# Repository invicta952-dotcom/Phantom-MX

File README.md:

# Phantom-MX

##   what is this??
Phantom-mx is cutom made keyboard with 87 mechincal switches, roatary encoder and custom built case and qmk firmware. It has 2 layer of functions to switch between as per your need. the case type is integrated plate mount which mean you dont need to lock the plate with case with 1000's of screw

---
##   why phantom-mx??
you may find many other custom keyboard with more features and better than this, but the one thing you will never find is perfect keyboard which is in budget and also meet your needs perfectly. it was built to meet my needs and also in budget. 
<br>
**bonus point**:- it has some really cool silkscreen

---
##   how to assemble it??
### 1. Ordering the PCB
1. **Download Production Files**: Navigate to the `PCB/` directory in this repository and download the Gerber zip file (e.g., `Gerber_Phantom-MX.zip`). Do not extract it.
2. **Choose a Manufacturer**: Upload the zip file to a PCB fabrication service such as JLCPCB, PCBWay, or OSH Park.
3. **Configure Board Settings**: Use the following standard specifications:
   * **Layers**: 2 Layers
   * **Thickness**: 1.6 mm
   * **Surface Finish**: HASL (or ENIG for better pad durability)
4. **Assembly (Optional)**: If you prefer factory assembly for surface-mount components (diodes/sockets), upload the BOM (Bill of Materials) and CPL (Component Placement List / Centroid file) provided in the repository to their PCBA service.

---

### 3. Hardware Assembly
1. **Solder Diodes**: Always solder small, low-profile components first. solder the diodes before the swithces for easy soldering.
2. **Solder Sockets/Switches**: solder the switches by passing them from top plate and then top layer of pcb.
3. **Mount the Pi Pico**: Place the Pi Pico onto its designated footprint. solder it in backside of the pcb.

---
# Images

#   case

---

#   zine

---

#   pcb

<br>
<br>
<br>
onshape link <br>
https://cad.onshape.com/documents/175f6b23ffbe170e5e8f7975/w/d68c6b2354c565e22789bc76/e/012a72f814c196a96be20986?renderMode=0&uiState=6a2fc775a442fa85ac58f430

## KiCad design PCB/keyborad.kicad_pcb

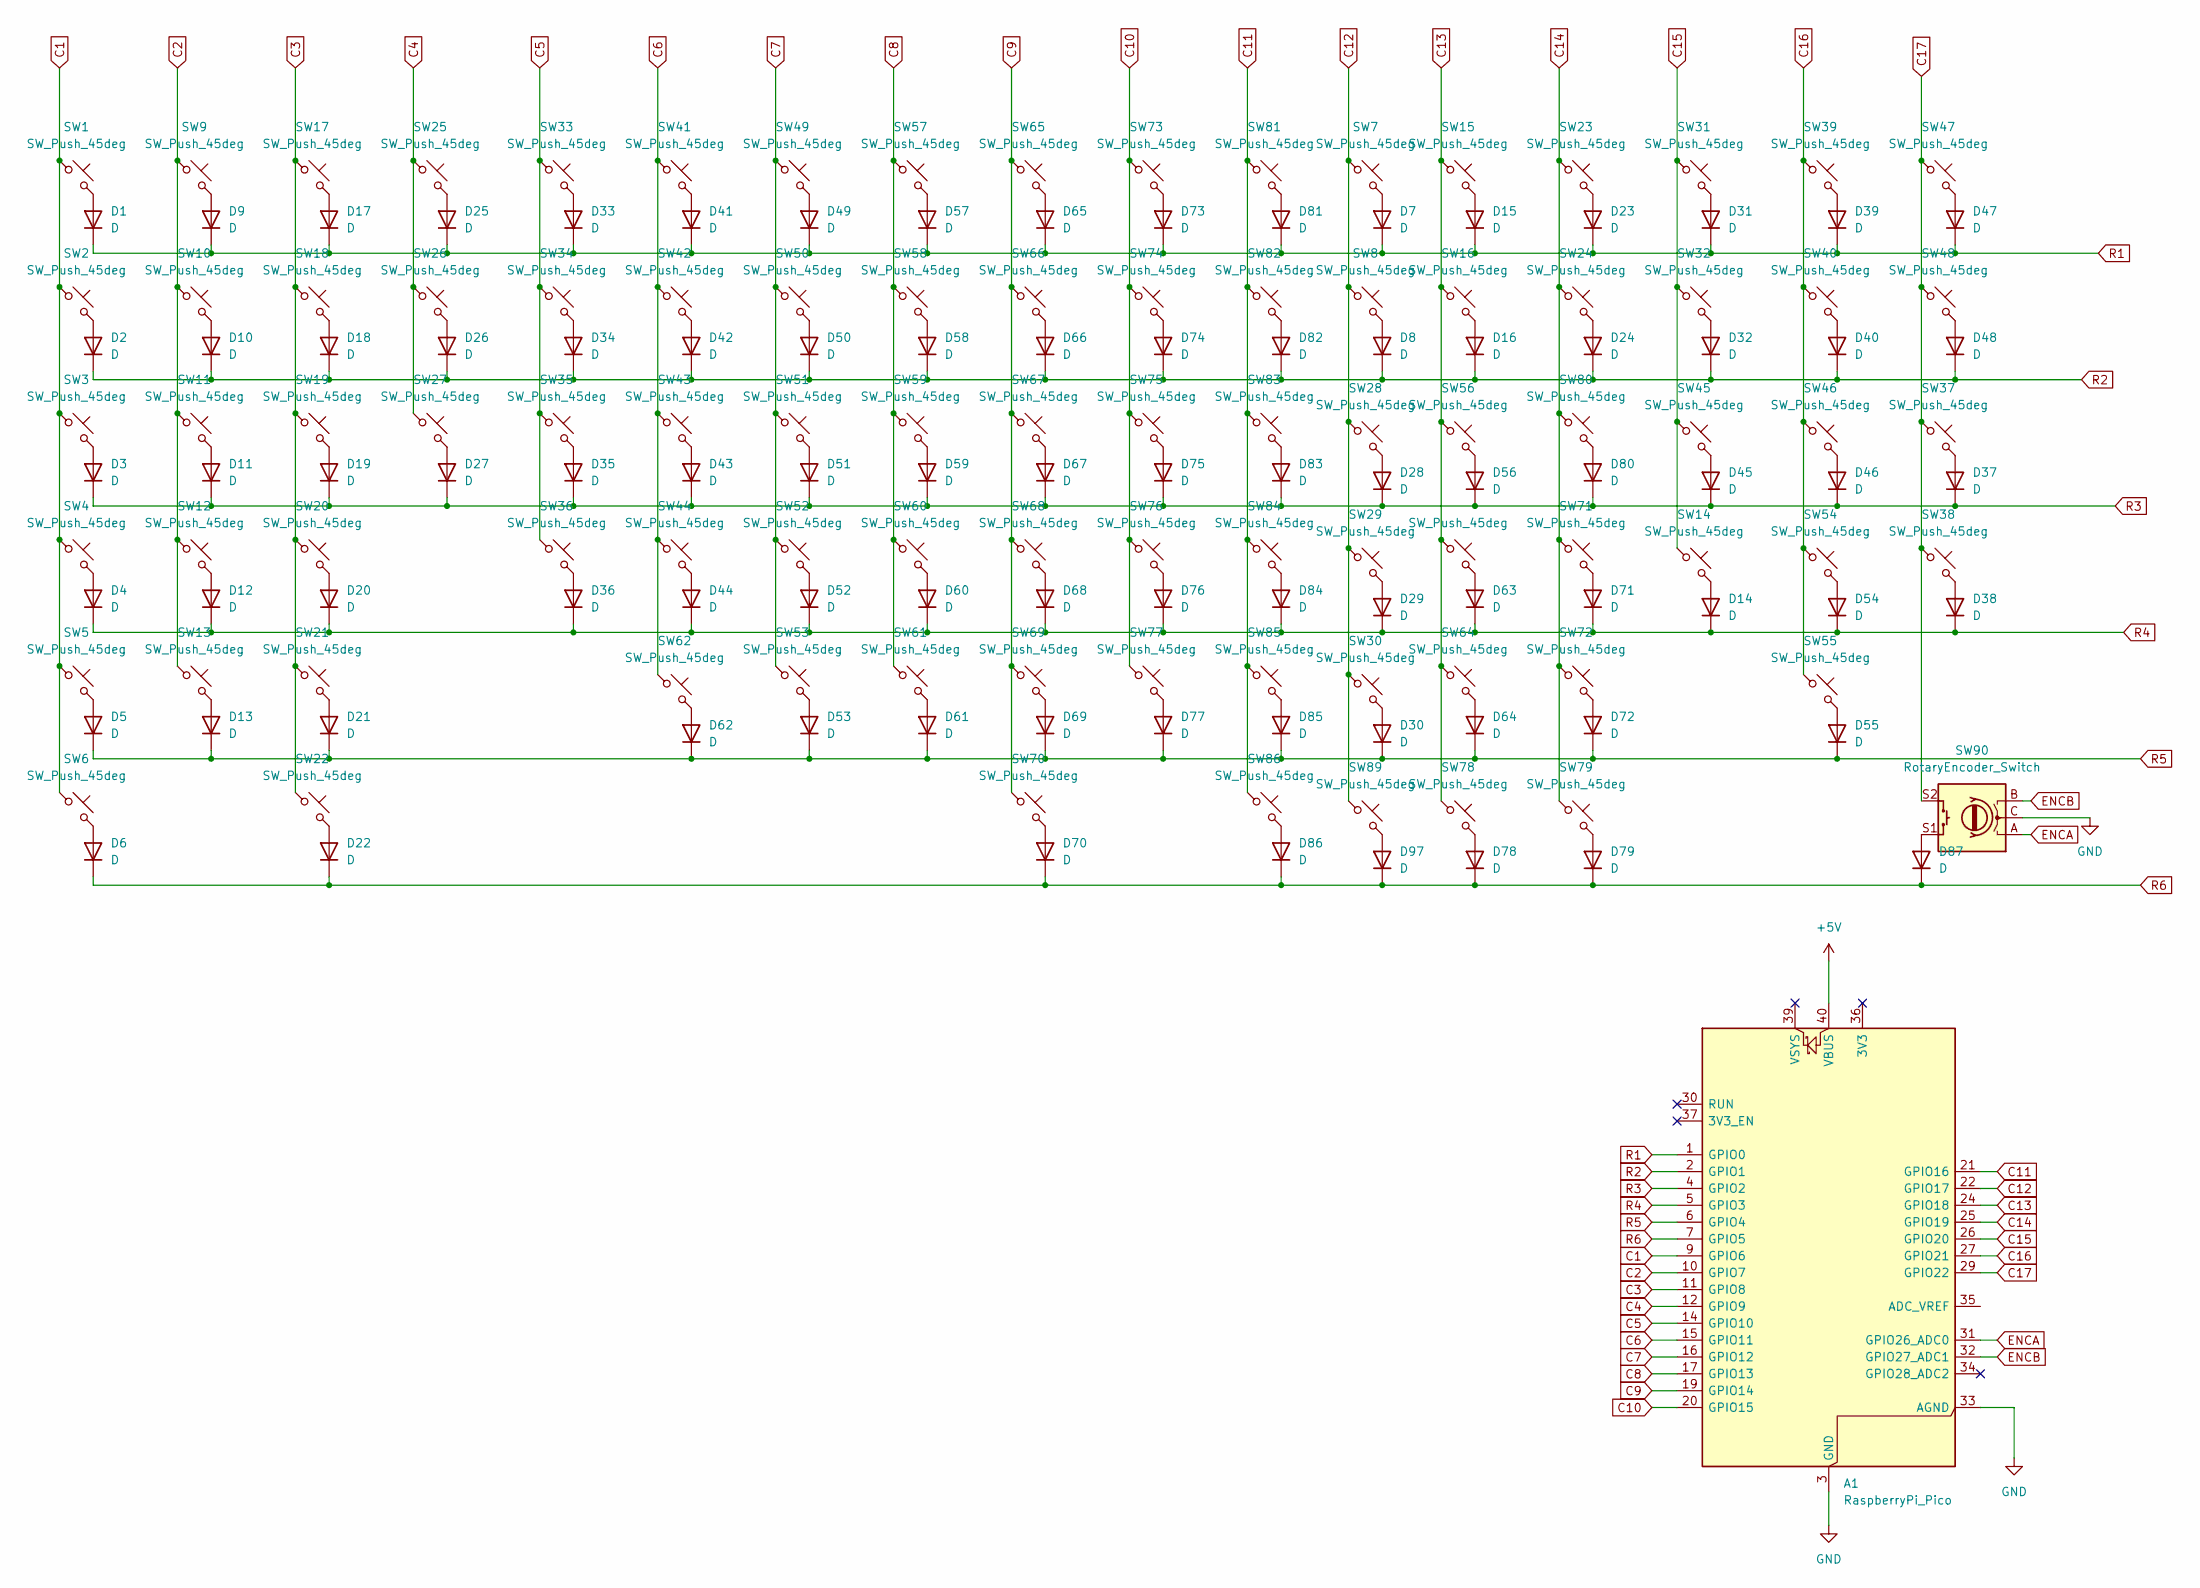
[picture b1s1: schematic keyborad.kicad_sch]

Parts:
A1: RaspberryPi_Pico; RaspberryPi_Pico_Common_Unspecified
D1, D2, D3, D4, D5, D6, D7, D8, D9, D10, D11, D12, D13, D14, D15, D16, D17, D18, D19, D20, D21, D22, D23, D24, D25, D26, D27, D28, D29, D30, D31, D32, D33, D34, D35, D36, D37, D38, D39, D40, D41, D42, D43, D44, D45, D46, D47, D48, D49, D50, D51, D52, D53, D54, D55, D56, D57, D58, D59, D60, D61, D62, D63, D64, D65, D66, D67, D68, D69, D70, D71, D72, D73, D74, D75, D76, D77, D78, D79, D80, D81, D82, D83, D84, D85, D86, D87, D97: D; DIODE
SW1, SW2, SW7, SW8, SW9, SW10, SW11, SW12, SW14, SW15, SW16, SW17, SW18, SW19, SW20, SW21, SW23, SW25, SW26, SW27, SW28, SW29, SW30, SW31, SW32, SW33, SW34, SW35, SW36, SW37, SW38, SW39, SW40, SW41, SW42, SW43, SW44, SW45, SW46, SW47, SW48, SW49, SW50, SW51, SW52, SW53, SW54, SW55, SW56, SW57, SW58, SW59, SW60, SW61, SW62, SW63, SW64, SW65, SW66, SW67, SW68, SW69, SW73, SW74, SW75, SW76, SW77, SW81, SW82, SW83, SW84, SW85: SW_Push_45deg; SW_Cherry_MX_1.00u_PCB
SW3, SW80: SW_Push_45deg; SW_Cherry_MX_1.50u_PCB
SW4: SW_Push_45deg; SW_Cherry_MX_1.75u_PCB
SW5, SW71: SW_Push_45deg; SW_Cherry_MX_2.25u_PCB
SW6, SW13, SW22, SW78, SW79, SW86, SW89: SW_Push_45deg; SW_Cherry_MX_1.25u_PCB
SW24: SW_Push_45deg; SW_Cherry_MX_2.00u_PCB
SW70: SW_Push_45deg; SW_Cherry_MX_6.25u_PCB
SW72: SW_Push_45deg; SW_Cherry_MX_2.75u_PCB
SW90: RotaryEncoder_Switch; RotaryEncoder_Alps_EC11E-Switch_Vertical_H20mm

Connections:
+5V: A1.40 (VBUS)
C1: A1.9 (GPIO6), SW1.1, SW2.1, SW3.1, SW4.1, SW5.1, SW6.1
C2: A1.10 (GPIO7), SW9.1, SW10.1, SW11.1, SW12.1, SW13.1
C3: A1.11 (GPIO8), SW17.1, SW18.1, SW19.1, SW20.1, SW21.1, SW22.1
C4: A1.12 (GPIO9), SW25.1, SW26.1, SW27.1
C5: A1.14 (GPIO10), SW33.1, SW34.1, SW35.1, SW36.1
C6: A1.15 (GPIO11), SW41.1, SW42.1, SW43.1, SW44.1, SW62.1
C7: A1.16 (GPIO12), SW49.1, SW50.1, SW51.1, SW52.1, SW53.1
C8: A1.17 (GPIO13), SW57.1, SW58.1, SW59.1, SW60.1, SW61.1
C9: A1.19 (GPIO14), SW65.1, SW66.1, SW67.1, SW68.1, SW69.1, SW70.1
C10: A1.20 (GPIO15), SW73.1, SW74.1, SW75.1, SW76.1, SW77.1
C11: A1.21 (GPIO16), SW81.1, SW82.1, SW83.1, SW84.1, SW85.1, SW86.1
C12: A1.22 (GPIO17), SW7.1, SW8.1, SW28.1, SW29.1, SW30.1, SW89.1
C13: A1.24 (GPIO18), SW15.1, SW16.1, SW56.1, SW63.1, SW64.1, SW78.1
C14: A1.25 (GPIO19), SW23.1, SW24.1, SW71.1, SW72.1, SW79.1, SW80.1
C15: A1.26 (GPIO20), SW14.1, SW31.1, SW32.1, SW45.1
C16: A1.27 (GPIO21), SW39.1, SW40.1, SW46.1, SW54.1, SW55.1
C17: A1.29 (GPIO22), SW37.1, SW38.1, SW47.1, SW48.1, SW90.S2
ENCA: A1.31 (GPIO26_ADC0), SW90.A
ENCB: A1.32 (GPIO27_ADC1), SW90.B
GND: A1.3 (GND), A1.8 (GND), A1.13 (GND), A1.18 (GND), A1.23 (GND), A1.28 (GND), A1.33 (AGND), A1.38 (GND), SW90.C
unnamed: D1.2 (A), SW1.2
unnamed: D2.2 (A), SW2.2
unnamed: D3.2 (A), SW3.2
unnamed: D4.2 (A), SW4.2
unnamed: D5.2 (A), SW5.2
unnamed: D6.2 (A), SW6.2
unnamed: D7.2 (A), SW7.2
unnamed: D8.2 (A), SW8.2
unnamed: D9.2 (A), SW9.2
unnamed: D10.2 (A), SW10.2
unnamed: D11.2 (A), SW11.2
unnamed: D12.2 (A), SW12.2
unnamed: D13.2 (A), SW13.2
unnamed: D14.2 (A), SW14.2
unnamed: D15.2 (A), SW15.2
unnamed: D16.2 (A), SW16.2
unnamed: D17.2 (A), SW17.2
unnamed: D18.2 (A), SW18.2
unnamed: D19.2 (A), SW19.2
unnamed: D20.2 (A), SW20.2
unnamed: D21.2 (A), SW21.2
unnamed: D22.2 (A), SW22.2
unnamed: D23.2 (A), SW23.2
unnamed: D24.2 (A), SW24.2
unnamed: D25.2 (A), SW25.2
unnamed: D26.2 (A), SW26.2
unnamed: D27.2 (A), SW27.2
unnamed: D28.2 (A), SW28.2
unnamed: D29.2 (A), SW29.2
unnamed: D30.2 (A), SW30.2
unnamed: D31.2 (A), SW31.2
unnamed: D32.2 (A), SW32.2
unnamed: D33.2 (A), SW33.2
unnamed: D34.2 (A), SW34.2
unnamed: D35.2 (A), SW35.2
unnamed: D36.2 (A), SW36.2
unnamed: D37.2 (A), SW37.2
unnamed: D38.2 (A), SW38.2
unnamed: D39.2 (A), SW39.2
unnamed: D40.2 (A), SW40.2
unnamed: D41.2 (A), SW41.2
unnamed: D42.2 (A), SW42.2
unnamed: D43.2 (A), SW43.2
unnamed: D44.2 (A), SW44.2
unnamed: D45.2 (A), SW45.2
unnamed: D46.2 (A), SW46.2
unnamed: D47.2 (A), SW47.2
unnamed: D48.2 (A), SW48.2
unnamed: D49.2 (A), SW49.2
unnamed: D50.2 (A), SW50.2
unnamed: D51.2 (A), SW51.2
unnamed: D52.2 (A), SW52.2
unnamed: D53.2 (A), SW53.2
unnamed: D54.2 (A), SW54.2
unnamed: D55.2 (A), SW55.2
unnamed: D56.2 (A), SW56.2
unnamed: D57.2 (A), SW57.2
unnamed: D58.2 (A), SW58.2
unnamed: D59.2 (A), SW59.2
unnamed: D60.2 (A), SW60.2
unnamed: D61.2 (A), SW61.2
unnamed: D62.2 (A), SW62.2
unnamed: D63.2 (A), SW63.2
unnamed: D64.2 (A), SW64.2
unnamed: D65.2 (A), SW65.2
unnamed: D66.2 (A), SW66.2
unnamed: D67.2 (A), SW67.2
unnamed: D68.2 (A), SW68.2
unnamed: D69.2 (A), SW69.2
unnamed: D70.2 (A), SW70.2
unnamed: D71.2 (A), SW71.2
unnamed: D72.2 (A), SW72.2
unnamed: D73.2 (A), SW73.2
unnamed: D74.2 (A), SW74.2
unnamed: D75.2 (A), SW75.2
unnamed: D76.2 (A), SW76.2
unnamed: D77.2 (A), SW77.2
unnamed: D78.2 (A), SW78.2
unnamed: D79.2 (A), SW79.2
unnamed: D80.2 (A), SW80.2
unnamed: D81.2 (A), SW81.2
unnamed: D82.2 (A), SW82.2
unnamed: D83.2 (A), SW83.2
unnamed: D84.2 (A), SW84.2
unnamed: D85.2 (A), SW85.2
unnamed: D86.2 (A), SW86.2
unnamed: D87.2 (A), SW90.S1
unnamed: D97.2 (A), SW89.2
R1: A1.1 (GPIO0), D1.1 (K), D7.1 (K), D9.1 (K), D15.1 (K), D17.1 (K), D23.1 (K), D25.1 (K), D31.1 (K), D33.1 (K), D39.1 (K), D41.1 (K), D47.1 (K), D49.1 (K), D57.1 (K), D65.1 (K), D73.1 (K), D81.1 (K)
R2: A1.2 (GPIO1), D2.1 (K), D8.1 (K), D10.1 (K), D16.1 (K), D18.1 (K), D24.1 (K), D26.1 (K), D32.1 (K), D34.1 (K), D40.1 (K), D42.1 (K), D48.1 (K), D50.1 (K), D58.1 (K), D66.1 (K), D74.1 (K), D82.1 (K)
R3: A1.4 (GPIO2), D3.1 (K), D11.1 (K), D19.1 (K), D27.1 (K), D28.1 (K), D35.1 (K), D37.1 (K), D43.1 (K), D45.1 (K), D46.1 (K), D51.1 (K), D56.1 (K), D59.1 (K), D67.1 (K), D75.1 (K), D80.1 (K), D83.1 (K)
R4: A1.5 (GPIO3), D4.1 (K), D12.1 (K), D14.1 (K), D20.1 (K), D29.1 (K), D36.1 (K), D38.1 (K), D44.1 (K), D52.1 (K), D54.1 (K), D60.1 (K), D63.1 (K), D68.1 (K), D71.1 (K), D76.1 (K), D84.1 (K)
R5: A1.6 (GPIO4), D5.1 (K), D13.1 (K), D21.1 (K), D30.1 (K), D53.1 (K), D55.1 (K), D61.1 (K), D62.1 (K), D64.1 (K), D69.1 (K), D72.1 (K), D77.1 (K), D85.1 (K)
R6: A1.7 (GPIO5), D6.1 (K), D22.1 (K), D70.1 (K), D78.1 (K), D79.1 (K), D86.1 (K), D87.1 (K), D97.1 (K)

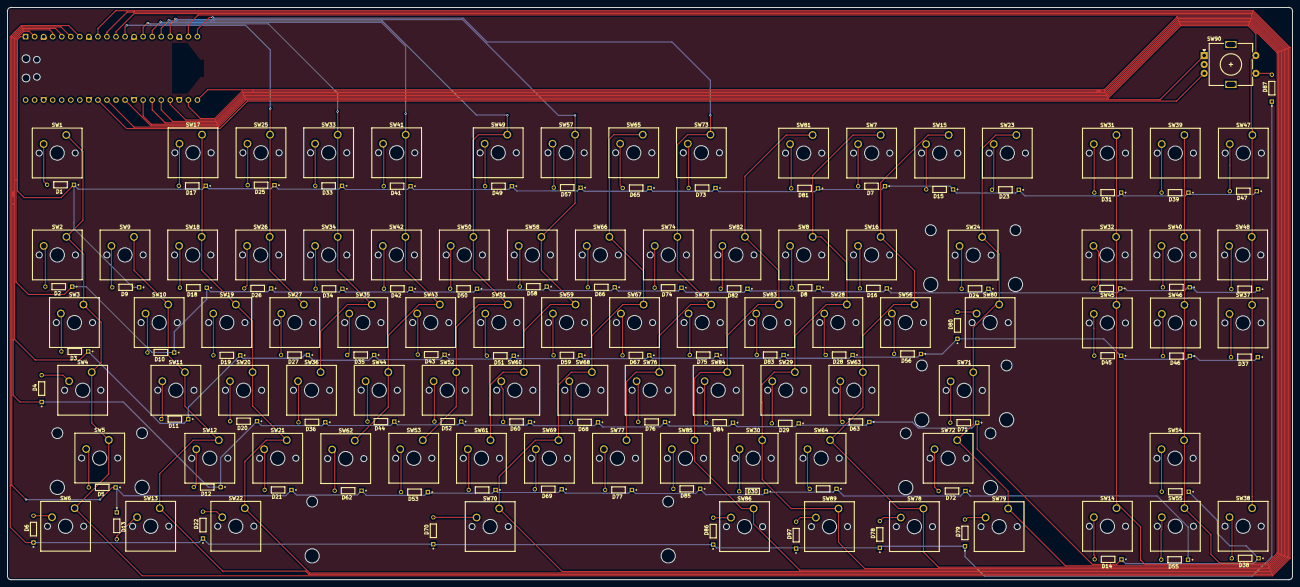
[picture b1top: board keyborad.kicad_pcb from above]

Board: 2 copper layers, 360.9 x 160.7 mm, 177 parts (1 on the bottom side), 114 nets.

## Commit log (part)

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2026-06-02 Create ingnore
2026-06-04 Create ignore
2026-06-04 Rename keyborad (1).step to bottom.step
2026-06-04 Create keyboard
2026-06-04 Rename keyborad-.zip to keyborad-grb-.zip
2026-06-04 Rename keyborad.pdf to keyborad-schnematics.pdf
2026-06-06 Create ZINE
2026-06-12 Create xyz
2026-06-12 Rename keyborad-grb-.zip to grb.zip
2026-06-12 Rename ingnore to .gitignore
2026-06-12 Rename ignore to .gitignore
2026-06-13 added case.step to case
